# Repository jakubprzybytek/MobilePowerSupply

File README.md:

# MobilePowerSupply
Mobile Power Supply

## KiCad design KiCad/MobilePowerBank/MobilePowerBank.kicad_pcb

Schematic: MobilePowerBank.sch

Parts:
C1, C5, C11, C28, C45, C46, C71: 47u/35V; CP_Tantalum_Case-D_EIA-7343-31_Reflow
C2, C29, C30, C47, C48, C72: 10u/50V/X7R; C_2220
C3: 4n7; C_0805
C4, C33, C34, C51, C52, C73, C74: 22n; C_0805
C6, C7, C8, C13, C15, C16, C18, C20, C26, C39, C40, C41, C42, C57, C58, C59, C60, C63, C65, C67, C69, C77, C78: 100n; C_0805
C9, C10, C35, C36, C37, C38, C53, C54, C55, C56: 47u/1-45mESR; CP_Tantalum_Case-D_EIA-7343-31_Reflow
C12: 220n; C_0805
C14: 47u/16V; CP_Tantalum_Case-C_EIA-6032-28_Reflow
C17: 47u/6.3V; CP_Tantalum_Case-C_EIA-6032-28_Reflow
C19, C21, C64, C66, C68, C70: 10u/6.3V; CP_Tantalum_Case-B_EIA-3528-21_Reflow
C22, C23: 10u/16V; CP_Tantalum_Case-B_EIA-3528-21_Reflow
C24, C25, C27, C43, C44, C61, C62, C79: 1u; C_0805
C31, C32: 10n; C_0805
C49, C50: 4u7; C_0805
C75: 330n / 50V; C_0805
C76: 22u/16V; CP_Elec_4x5.8
C80, C82, C83, C84, C85, C86: 1u/50V; C_1206
C81: 100u/6V3; C_1812
D1: LED; D_0805
F1: 5A; Fuseholder5x20_horiz_open_inline_Type-I
J1: Power IN; TerminalBlock_Altech_AK300-2_P5.00mm
J2: Power OUT 2; TerminalBlock_Altech_AK300-2_P5.00mm
J3: Power OUT 1; TerminalBlock_Altech_AK300-2_P5.00mm
J4: OLED I2C; OLED_0.96inch_128x64_I2C
J5: PDI; Pin_Header_Straight_2x03_Pitch2.54mm
J6: OLED; FPC_30
J7: Power OUT 3; TerminalBlock_Altech_AK300-2_P5.00mm
J8: Power OUT 4; TerminalBlock_Altech_AK300-2_P5.00mm
J9: Power OUT 5; TerminalBlock_Altech_AK300-2_P5.00mm
J10: Power OUT 6; TerminalBlock_Altech_AK300-2_P5.00mm
J11: PowerLED; JST_XH_B02B-XH-A_02x2.50mm_Straight
L1: 10u; L_1206
MH1, MH2, MH3, MH4: MountingHole_Pad; MountingHole_3.5mm
R1, R6, R87: 68k; R_0805
R2, R9, R10, R21, R38, R39, R66, R67: 2k2; R_0805
R3, R14, R16, R17, R18, R19, R48, R49, R50, R51, R52, R53, R76, R77, R78, R79, R80, R81, R94, R95, R96: 0R033; R_2512
R4, R15, R20, R36, R37, R54, R55, R64, R65, R82, R83, R97: 20k; R_0805
R5, R12, R86: 100k; R_0805
R7, R27, R33, R35, R61, R63: 300k; R_0805
R8, R11, R23, R24, R47, R73, R75, R93: 10k; R_0805
R13, R28: 4k7; R_0805
R22, R29, R31, R44, R57, R59: 47k; R_0805
R25: 1M; R_1206
R26, R30, R56, R58: 220k; R_0805
R32, R34, R60, R62: 30k; R_0805
R40, R41, R42, R43, R68, R69, R70, R71: 15k4; R_0805
R45: 3k9; R_0805
R46, R72, R74, R92: 90k; R_0805
R84, R85, R98: 0; R_0805
R88: 11k; R_0805
R89: 1k5; R_0805
R90: 7k68; R_0805
R91: 200; R_0805
R99: 3k3; R_0805
SW1: SW_DIP_x01; Pin_Header_Angled_1x02_Pitch2.54mm
U1, U4, U9, U10, U13, U14, U16: INA139; SOT-23-5
U2, U7, U8: LMZ14203H; TO-263-7_TabPin4
U3: L78M12; TO-252-2_Rectifier
U5: UA78M33; TO-252-2_Rectifier
U6: LMZ14203; TO-263-7_TabPin4
U11, U12: LMZ14201H; TO-263-7_TabPin4
U15: ATXMEGA256A3U-AU; TQFP-64_14x14mm_Pitch0.8mm
U17: L78L05_SOT89; SOT-89-3
x1, x2, x3, x4, x6, x7, x8: jumper; Jumper_33x1.5
x5, x9: jumper; Jumper_45x1.5

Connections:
+3V3: C16.1, C17.1, C18.1, C19.1, C24.1, C63.1, C64.1, C65.1, C66.1, C67.1, C68.1, C69.1, C70.1, D1.2, J4.1, J5.2, J6.19, J6.20, J6.21, L1.1, R9.2, R10.2, R23.2, R24.1, U5.3 (OUT), U15.15 (VCC), U15.25 (VCC), U15.35 (VCC), U15.45 (VCC), U15.53 (VCC)
/+3.3VA: C20.1, C21.1, L1.2, U15.61 (AVCC)
/OLED_!DS: J6.17, U15.28 (RXD0/OC0C/PD2)
/OLED_!RES: J6.16, U15.31 (PD5/OC1B/XCK1/MOSI)
/OLED_D0: J6.12, U15.36 (PE0/OC0A/SDA/SDAIN)
/OLED_D1: J6.11, U15.37 (PE1/OC0B/XCK0/SCL/SCLIN)
/OLED_D2: J6.10, U15.38 (PE2/OC0C/RXD0/SDAOUT)
/OLED_D3: J6.9, U15.39 (PE3/OC0D/TXD0/SCLOUT)
/OLED_D4: J6.8, U15.40 (PE4/OC1A/~SS~)
/OLED_D5: J6.7, U15.41 (PE5/OC1B/XCK1/MOSI)
/OLED_D6: J6.6, U15.42 (PE6/RXD1/MISO/TOSC2)
/OLED_D7: J6.5, U15.43 (PE7/TXD1/SCK/TOSC1)
/OLED_D/!C: J6.15, U15.29 (TXD0/OC0D/PD3)
/OLED_E/!RD: J6.13, U15.30 (PD4/OC1A/~SS~)
/OLED_R/!W: J6.14, U15.32 (PD6/RXD1/D-/MISO)
GND: C5.2, C6.2, C12.2, C13.2, C14.2, C15.2, C16.2, C17.2, C18.2, C19.2, C20.2, C21.2, C22.2, C23.2, C24.2, C25.2, C26.2, C27.2, C39.2, C40.2, C43.2, C44.2, C57.2, C58.2, C61.2, C62.2, C63.2, C64.2, C65.2, C66.2, C67.2, C68.2, C69.2, C70.2, C77.2, C79.2, J4.2, J5.6, J6.1, J6.29, R25.1, R98.1, SW1.1, U3.2 (GND), U5.2 (GND), U15.14 (GND), U15.24 (GND), U15.34 (GND), U15.44 (GND), U15.52 (GND), U15.60 (GND)
GNDA: C1.2, C2.2, C3.2, C7.1, C8.1, C9.2, C10.2, C11.2, C28.2, C29.2, C30.2, C31.2, C32.2, C35.2, C36.2, C37.2, C38.2, C41.1, C42.1, C45.2, C46.2, C47.2, C48.2, C49.2, C50.2, C53.2, C54.2, C55.2, C56.2, C59.1, C60.1, C71.2, C72.2, C73.2, C75.2, C76.2, C78.1, C80.2, C81.2, C82.2, C83.1, C84.2, C85.2, C86.2, J1.1, J2.2, J3.2, J7.2, J8.2, J9.2, J10.2, J11.2, R2.2, R4.2, R13.2, R15.2, R20.2, R21.2, R36.2, R37.2, R38.2, R39.2, R45.2, R47.2, R54.2, R55.2, R64.2, R65.2, R66.2, R67.2, R73.2, R75.2, R82.2, R83.2, R88.2, R89.2, R93.2, R97.2, R98.2, U1.2, U2.4, U4.2, U6.4, U7.4, U8.4, U9.2, U10.2, U11.4, U12.4, U13.2, U14.2, U16.2, x6.1 (A), x6.2 (B), x7.1 (A), x7.2 (B), x8.1 (A), x8.2 (B), x9.1 (A), x9.2 (B)
IN_Current: C25.1, R4.1, U1.1, U15.11 (TDI/AC5/ADC5/PB5)
IN_Voltage: C15.1, R1.2, R2.1, U15.12 (TCK/AC1OUT/AC6/ADC6/PB6)
LED: R8.1, U15.48 (PF2/OC0C/RXD0)
unnamed: C3.1, U2.5
unnamed: C4.2, R21.1, R22.1, U2.6
unnamed: C5.1, C6.1, U3.1 (IN), x5.2 (B)
unnamed: C4.1, C8.2, C9.1, C10.1, C83.2, R14.2, R18.2, R19.2, R28.2, U2.7, U4.3, U4.5
unnamed: C23.1, J6.3
unnamed: C31.1, U7.5
unnamed: C32.1, U8.5
unnamed: C33.1, C35.1, C37.1, C41.2, C84.1, R42.2, R48.2, R49.2, R50.2, U7.7, U9.3, U9.5
unnamed: C33.2, R38.1, R40.1, U7.6
unnamed: C34.1, C36.1, C38.1, C42.2, C82.1, R43.2, R51.2, R52.2, R53.2, U8.7, U10.3, U10.5
unnamed: C34.2, R39.1, R41.1, U8.6
unnamed: C49.1, U11.5
unnamed: C50.1, U12.5
unnamed: C51.1, C53.1, C55.1, C59.2, C85.1, R70.2, R76.2, R77.2, R78.2, U11.7, U13.3, U13.5
unnamed: C51.2, R66.1, R68.1, U11.6
unnamed: C52.1, C54.1, C56.1, C60.2, C86.1, R71.2, R79.2, R80.2, R81.2, U12.7, U14.3, U14.5
unnamed: C52.2, R67.1, R69.1, U12.6
unnamed: C73.1, U6.5
unnamed: C74.1, C78.2, C80.1, C81.1, R91.2, R94.2, R95.2, R96.2, U6.7, U16.3, U16.5
unnamed: C74.2, R89.1, R90.1, U6.6
unnamed: C76.1, J11.1, R99.1, U17.2 (GND)
unnamed: D1.1, R8.2
unnamed: J6.4, R25.2
unnamed: R5.2, U2.2
unnamed: R6.2, R7.1
unnamed: R11.2, R23.1, SW1.2
unnamed: R7.2, R20.1, U2.3
unnamed: R22.2, R28.1
unnamed: R26.2, R32.1
unnamed: R5.1, R27.2
unnamed: R29.2, R33.1
unnamed: R30.2, R34.1
unnamed: R31.2, R35.1
unnamed: R32.2, U7.2
unnamed: R33.2, R36.1, U7.3
unnamed: R34.2, U8.2
unnamed: R35.2, R37.1, U8.3
unnamed: R40.2, R42.1
unnamed: R41.2, R43.1
unnamed: R56.2, R60.1
unnamed: R57.2, R61.1
unnamed: R58.2, R62.1
unnamed: R59.2, R63.1
unnamed: R60.2, U11.2
unnamed: R61.2, R64.1, U11.3
unnamed: R62.2, U12.2
unnamed: R63.2, R65.1, U12.3
unnamed: R68.2, R70.1
unnamed: R69.2, R71.1
unnamed: R84.2, R86.1
unnamed: R85.2, R87.1
unnamed: R86.2, U6.2
unnamed: R87.2, R88.1, U6.3
unnamed: R90.2, R91.1
unnamed: R99.2, U17.1 (OUT)
OUT_1_Current: C27.1, R15.1, U4.1, U15.3 (AC5/ADC5/PA5)
OUT_1_Voltage: C26.1, R12.2, R13.1, U15.4 (AC1OUT/AC6/ADC6/PA6)
OUT_2_Current: C43.1, R54.1, U9.1, U15.1 (AC3/ADC3/PA3)
OUT_2_Voltage: C39.1, R44.2, R45.1, U15.2 (AC4/ADC4/PA4)
OUT_3_Current: C44.1, R55.1, U10.1, U15.63 (AC1/ADC1/PA1)
OUT_3_Voltage: C40.1, R46.2, R47.1, U15.64 (AC2/ADC2/PA2)
OUT_4_Current: C61.1, R82.1, U13.1, U15.7 (AC1/ADC1/PB1)
OUT_4_Voltage: C57.1, R72.2, R73.1, U15.8 (DAC0/AC2/ADC2/PB2)
OUT_5_Current: C62.1, R83.1, U14.1, U15.5 (AC0OUT/AC7/ADC7/PA7)
OUT_5_Voltage: C58.1, R74.2, R75.1, U15.6 (AREFB/AC0/ADC0/PB0)
OUT_6_Current: C79.1, R97.1, U15.9 (DAC1/AC3/ADC3/PB3), U16.1
OUT_6_Voltage: C77.1, R92.2, R93.1, U15.10 (TMS/AC4/ADC4/PB4)
PDI_CLK: J5.5, R24.2, U15.57 (~RESET~/PDI_CLK)
PDI_DATA: J5.1, U15.56 (PDI_DATA)
POWER_1_OUT: J3.1, R12.1, R14.1, R18.1, R19.1, U4.4
POWER_2_OUT: J2.1, R44.1, R48.1, R49.1, R50.1, U9.4
POWER_3_OUT: J7.1, R46.1, R51.1, R52.1, R53.1, U10.4
POWER_4_OUT: J8.1, R72.1, R76.1, R77.1, R78.1, U13.4
POWER_5_OUT: J9.1, R74.1, R79.1, R80.1, R81.1, U14.4
POWER_6_OUT: J10.1, R92.1, R94.1, R95.1, R96.1, U16.4
POWER_IN: C11.1, C29.1, R3.1, R16.1, R17.1, R26.1, R29.1, U1.4, U7.1, x1.1 (A), x2.1 (A)
POWER_IN_1: C1.1, C2.1, R6.1, R27.1, U2.1, x2.2 (B), x3.1 (A)
POWER_IN_3: C28.1, C30.1, R30.1, R31.1, U8.1, x1.2 (B)
POWER_IN_4: C45.1, C46.1, C47.1, C48.1, R56.1, R57.1, R58.1, R59.1, U11.1, U12.1, x3.2 (B), x4.1 (A)
POWER_IN_6: C71.1, C72.1, R84.1, R85.1, U6.1, x4.2 (B), x5.1 (A)
SCK: J4.3, R9.1, U15.17 (SCLIN/SCL/XCK0/OC0AHS/OC0B/PC1)
SDA: J4.4, R10.1, U15.16 (SDAIN/SDA/~OC0ALS~/OC0A/PC0)
SWITCH: C12.1, R11.1, U15.49 (PF3/OC0D/TXD0)
Unfused_Power: C75.1, F1.1, J1.2, U17.3 (IN)
VDD: C7.2, F1.2, R1.1, R3.2, R16.2, R17.2, U1.3, U1.5

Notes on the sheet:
Dell Vout = 19.6V Iout(max) = 3A Uen = 22.9V SS 1 (Soft start order)
ASI1600 Vout = 12V Iout(max) = 3A SS 2
EQ6-R Vout = 12V Iout(max) = 3A SS 2
Moonlite Vout = 12V Iout(max) = 1A SS 1
FlatField Vout = 12V Iout(max) = 1A SS 1
USB Vout = 5V Iout(max) = 3A ss 3
R=5V/5mA=1k
3.9/(47+3.9) * 12V = 0.92V
4.7/(100+4.7) * 12V = 0.90V
2k2/(2k2+68k)=0.03 (1/32)

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
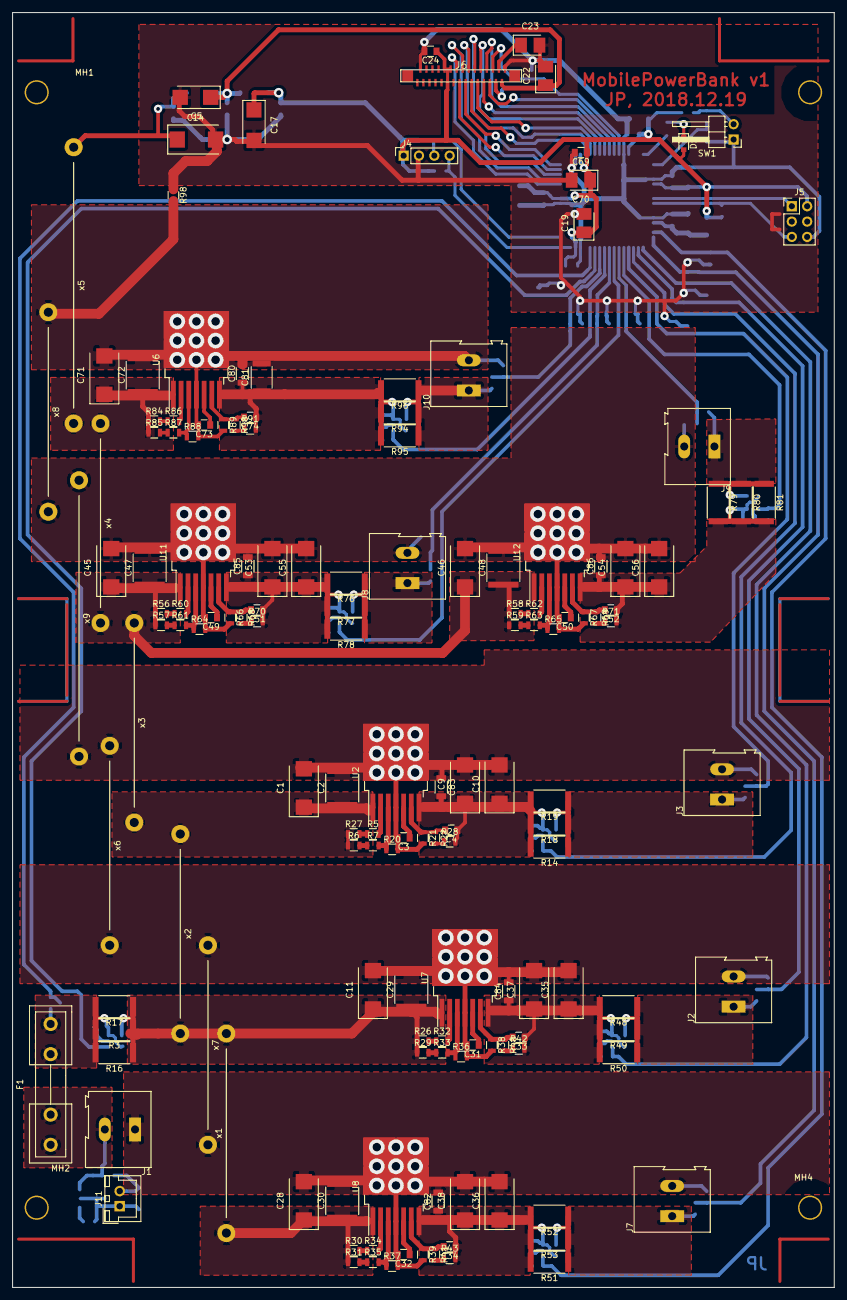
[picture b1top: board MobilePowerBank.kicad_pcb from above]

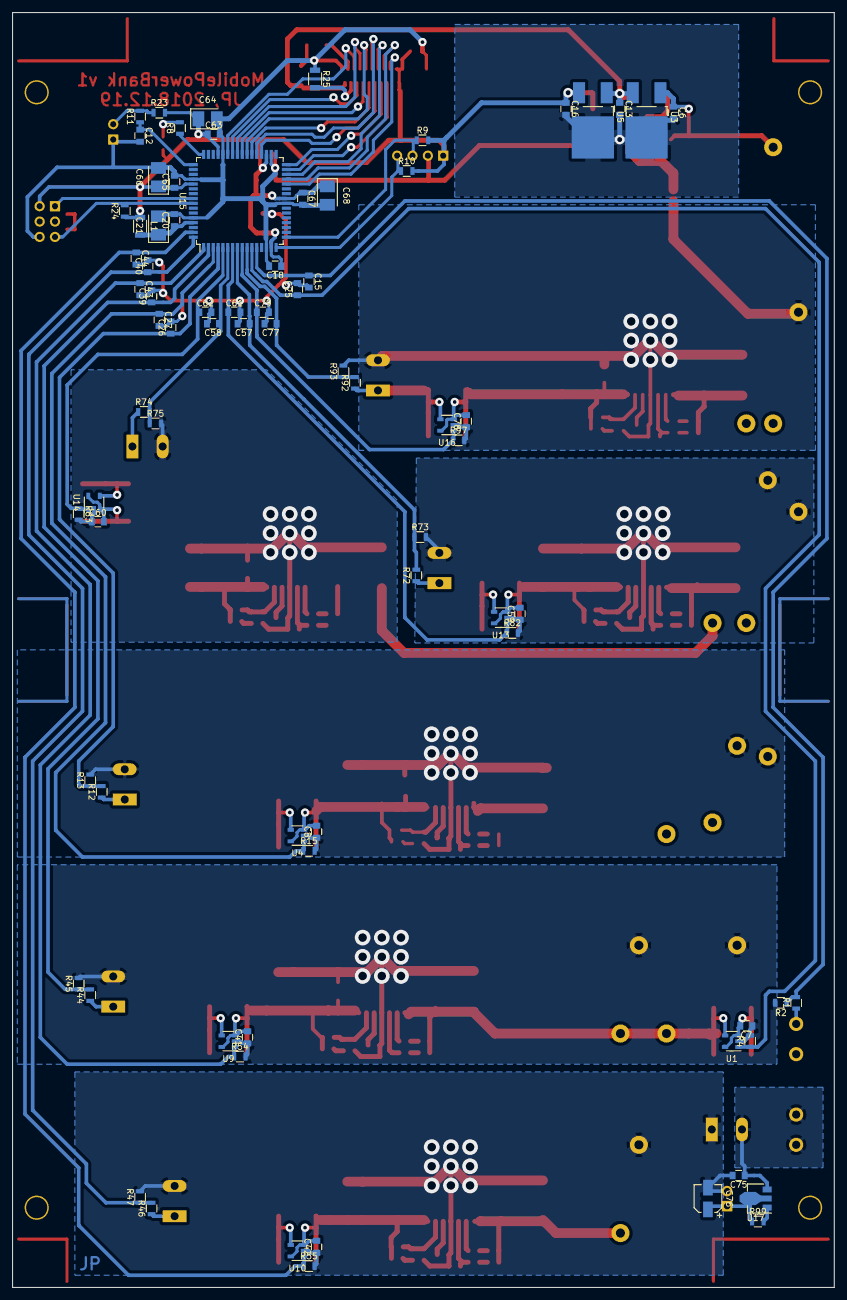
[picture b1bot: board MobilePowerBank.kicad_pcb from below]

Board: 2 copper layers, 136.0 x 211.0 mm, 230 parts (77 on the bottom side), 106 nets.

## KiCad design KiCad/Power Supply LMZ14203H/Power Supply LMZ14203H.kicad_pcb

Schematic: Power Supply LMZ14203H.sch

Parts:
C1, C5, C14: 100u; CP_Elec_6.3x7.7
C2: 10u/35V/X7R; C_2220
C3: 4u7; C_0805
C4: 22n; C_0805
C6, C7, C8, C13, C15, C16, C18, C20, C26: 100n; C_0805
C9, C10: 47u/1-45mESR; CP_Tantalum_Case-D_EIA-7343-31_Reflow
C12: 10n; C_0805
C17: 47u; CP_Elec_6.3x5.8
C19, C21, C22, C23: 10u; CP_Elec_4x5.8
C24, C25, C27: 1u; C_0805
D1: LED; D_0805
F1: 5A; Fuseholder5x20_horiz_open_inline_Type-I
J1: Power IN; TerminalBlock_Altech_AK300-2_P5.00mm
J3: Power OUT; TerminalBlock_Altech_AK300-2_P5.00mm
J4: OLED I2C; OLED_0.96inch_128x64_I2C
J5: PDI; Pin_Header_Straight_2x03_Pitch2.54mm
J6: OLED; FPC_30
L1: 10u; L_1206
R1: 68k; R_0805
R2, R9, R10, R21: 2k2; R_0805
R3, R14, R16, R17, R18, R19: 0R1; R_2512
R4, R15, R20: 20k; R_0805
R5, R6: 30k; R_0805
R7: 300k; R_0805
R8, R11, R13, R23, R24: 10k; R_0805
R12: 90k; R_0805
R22, R28: 15k4; R_0805
R25: 1M; R_1206
R26: 0; R_0805
R27: 220k; R_0805
SW1: SW_DIP_x01; SW_SPST_B3S-1000
U1, U4: INA169; SOT-23-5
U2: LMZ14203H; TO-263-7_TabPin4
U3: L78M12; TO-252-2_Rectifier
U5: UA78M33; TO-252-2_Rectifier
U6: ATXMEGA32E5-AU; TQFP-32_7x7mm_Pitch0.8mm

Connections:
+3V3: C16.1, C17.1, C18.1, C19.1, C24.1, D1.2, J4.1, J5.2, J6.19, J6.20, J6.21, L1.1, R9.2, R10.2, R23.2, R24.1, U5.3, U6.17 (VCC)
+12V: C13.1, C14.1, C22.1, J6.2, U3.3, U5.1
/+3.3VA: C20.1, C21.1, L1.2, U6.32 (AVCC)
/OLED_!DS: J6.17, U6.21 (PD7/ADC15/TXD0/IN3/CLKOUT/EVOUT/AC0OUT)
/OLED_!RES: J6.16, U6.22 (PD6/ADC14/RXD0/IN0/RTCOUT/AC1OUT)
/OLED_D0: J6.12, U6.9 (AC0OUT/IN3/MOSI/TXD0/OC4DHS/OC4D/PC7)
/OLED_D1: J6.11, U6.10 (AC1OUT/IN0/MISO/RXD0/~OC4DLS~/OC4C/PC6)
/OLED_D2: J6.10, U6.11 (IN2/SCK/XCK0/OC5B/OC4CHS/OC4B/PC5)
/OLED_D3: J6.9, U6.12 (EXTCLK/OUT0/IN1/~SS~/OC5A/~OC4CLS~/OC4A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)
/OLED_D4: J6.8, U6.13 (IN3/TXD0/OC4BHS/OC4D/PC3)
/OLED_D5: J6.7, U6.14 (IN0/RXD0/~OC4BLS~/OC4C/PC2)
/OLED_D6: J6.6, U6.15 (IN2/SCL/XCK0/OC4AHS/OC4B/PC1)
/OLED_D7: J6.5, U6.16 (OUT0/IN1/SDA/~OC4ALS~/OC4A/PC0)
/OLED_D/!C: J6.15, U6.23 (PD5/ADC13/OC5B/XCK0/IN2)
/OLED_E/!RD: J6.13, U6.25 (PD3/ADC11/TXD0/IN3/OC1)
/OLED_R/!W: J6.14, U6.24 (PD4/ADC12/OC5A/IN1/OUT0/CLKOUT/EVOUT)
GND: C5.2, C6.2, C7.1, C8.1, C12.2, C13.2, C14.2, C15.2, C16.2, C17.2, C18.2, C19.2, C20.2, C21.2, C22.2, C23.2, C24.2, C25.2, C26.2, C27.2, J4.2, J5.6, J6.1, J6.29, R2.2, R4.2, R13.2, R15.2, R25.1, R26.1, SW1.1, U1.2, U3.2, U4.2, U5.2, U6.1 (GND), U6.18 (GND)
GNDA: C1.2, C2.2, C3.2, C9.2, C10.2, J1.1, J3.2, R20.2, R21.2, R26.2, U2.4
IN_Current: C25.1, R4.1, U1.1, U6.3 (DAC1/AC3/ADC3/PA3)
IN_Voltage: C15.1, R1.2, R2.1, U6.4 (DAC0/AC2/ADC2/PA2)
LED: R8.1, U6.30 (AC1OUT/AC6/ADC6/PA6)
unnamed: C1.1, C2.1, R3.1, R6.1, R16.1, R17.1, R27.1, U1.4, U2.1
unnamed: C3.1, U2.5
unnamed: C4.2, R21.1, R22.1, U2.6
unnamed: C4.1, C8.2, C9.1, C10.1, R12.1, R14.2, R18.2, R19.2, R28.2, U2.7, U4.3, U4.5
unnamed: C23.1, J6.3
unnamed: D1.1, R8.2
unnamed: F1.1, J1.2
unnamed: J6.4, R25.2
unnamed: R5.2, U2.2
unnamed: R6.2, R7.1
unnamed: R11.2, R23.1, SW1.2
unnamed: R7.2, R20.1, U2.3
unnamed: R22.2, R28.1
unnamed: R5.1, R27.2
OUT_Current: C27.1, R15.1, U4.1, U6.6 (AREF/AC0/ADC0/PA0)
OUT_Voltage: C26.1, R12.2, R13.1, U6.5 (AC1/ADC1/PA1)
PDI_CLK: J5.5, R24.2, U6.8 (~RESET~/PDI_CLK)
PDI_DATA: J5.1, U6.7 (PDI_DATA)
POWER_IN: C5.1, C6.1, C7.2, F1.2, R1.1, R3.2, R16.2, R17.2, U1.3, U1.5, U3.1
POWER_OUT: J3.1, R14.1, R18.1, R19.1, U4.4
SCK: J4.3, R9.1, U6.27 (PD1/ADC1/XCK0/SCL/IN2)
SDA: J4.4, R10.1, U6.28 (PD0/ADC8/SDA/IN1/OUT0/AREF)
SWITCH: C12.1, R11.1, U6.29 (AC0OUT/AC7/ADC7/PA7)

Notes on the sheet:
Vout = 12V Iout(max) = 3A
Enable range 1.18-6.50V Rup/Rdown = (Uin/1.18)-1

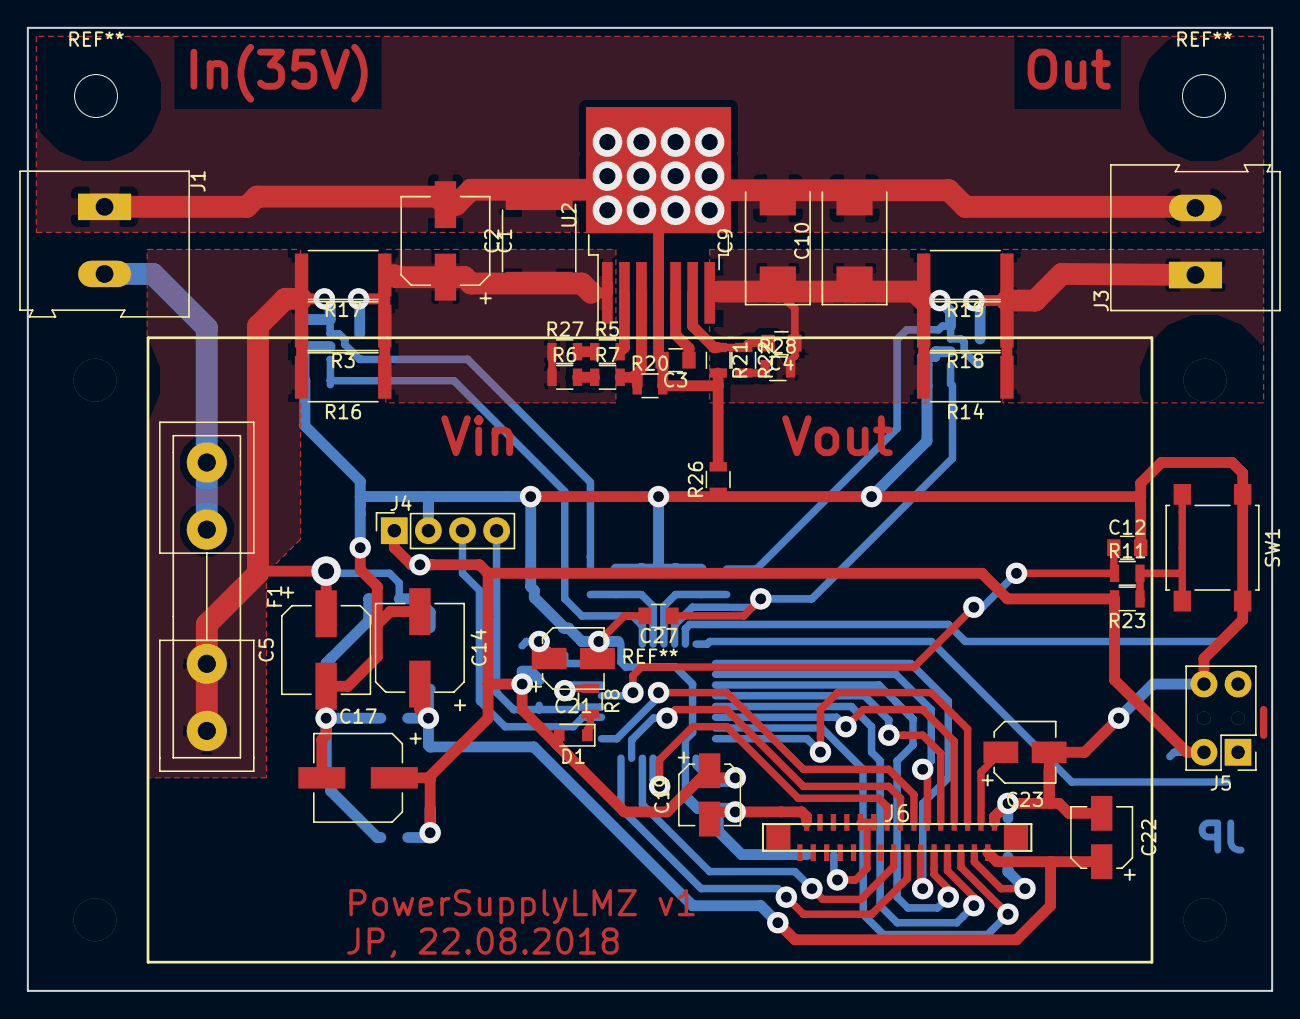
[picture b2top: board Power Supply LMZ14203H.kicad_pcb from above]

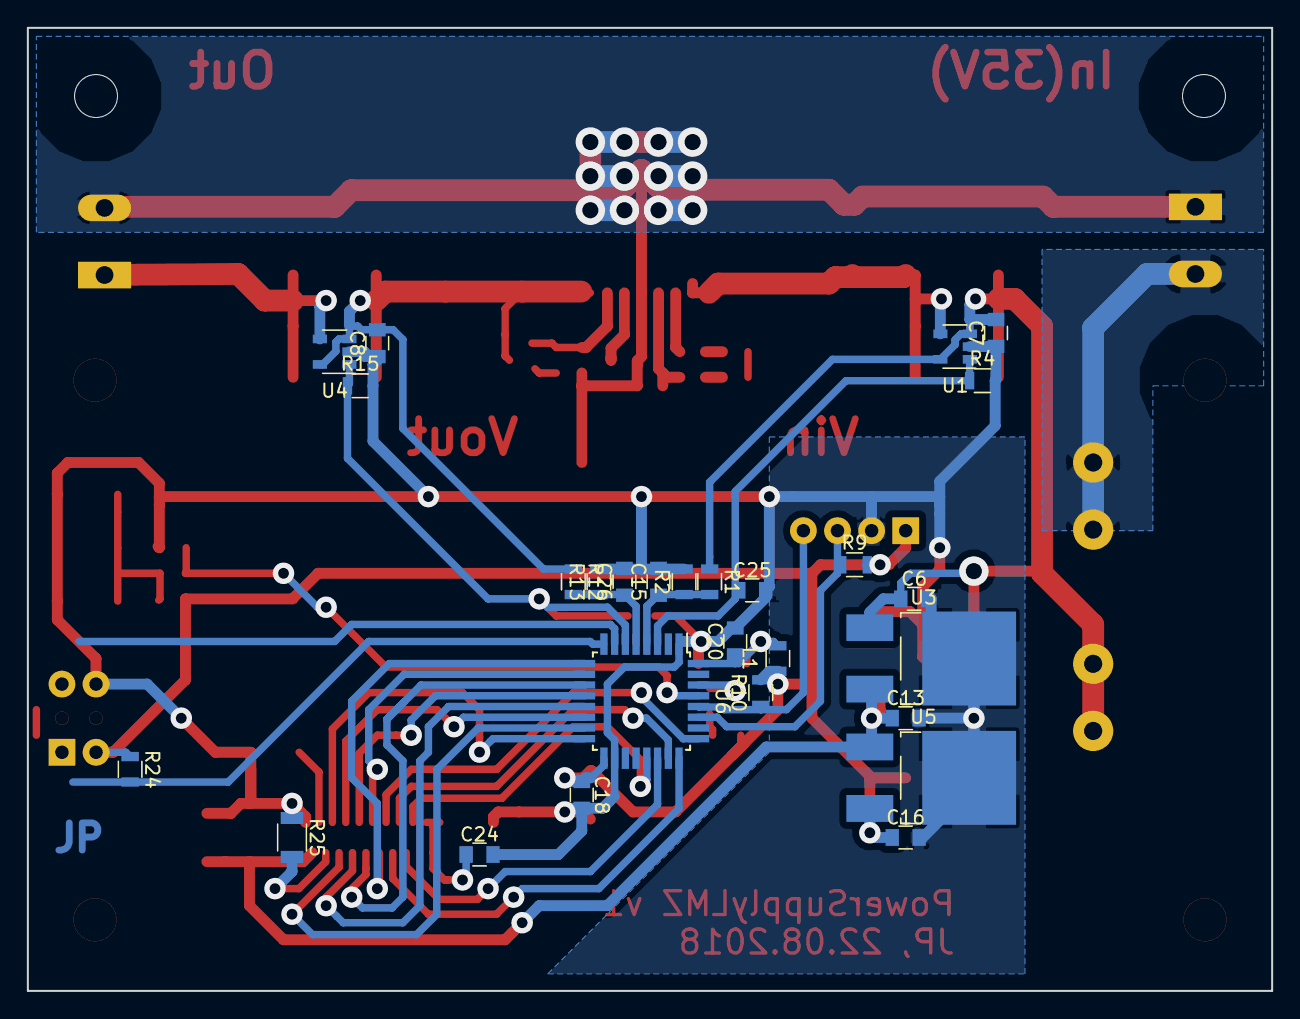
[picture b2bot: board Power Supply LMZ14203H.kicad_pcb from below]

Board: 2 copper layers, 92.7 x 71.8 mm, 69 parts (27 on the bottom side), 44 nets.

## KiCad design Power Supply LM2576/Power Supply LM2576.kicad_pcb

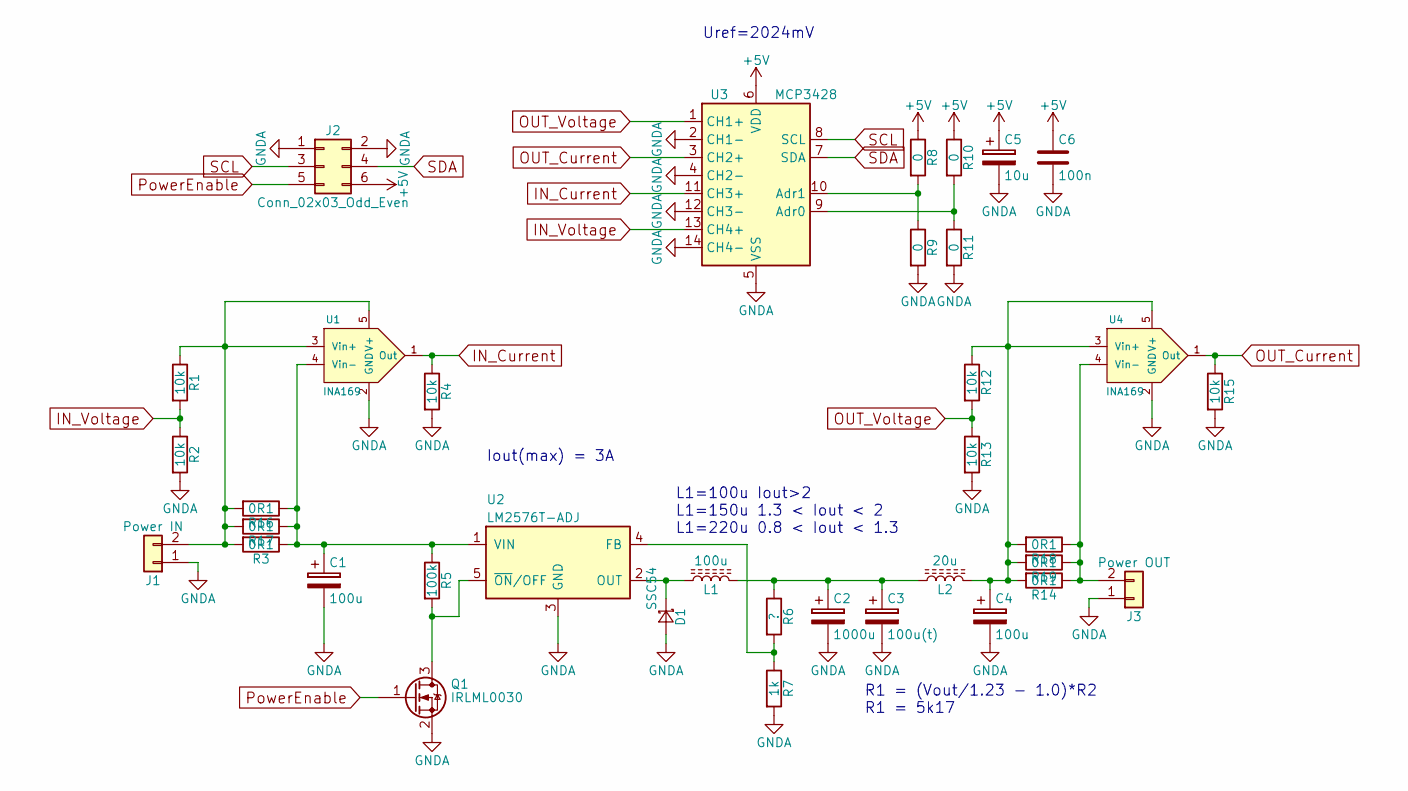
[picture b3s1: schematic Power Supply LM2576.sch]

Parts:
C1: 100u; CP_Radial_D8.0mm_P2.50mm
C2: 1000u; CP_Radial_D10.0mm_P2.50mm
C3: 100u(t); CP_Tantalum_Case-D_EIA-7343-31_Reflow
C4: 100u; CP_Radial_D6.3mm_P2.50mm
C5: 10u; CP_Radial_D6.3mm_P2.50mm
C6: 100n; C_0805
D1: SSC54; D_SMC
J1: Power IN; Pin_Header_Straight_1x02_Pitch2.54mm
J2: Conn_02x03_Odd_Even; Pin_Header_Straight_2x03_Pitch2.54mm
J3: Power OUT; Pin_Header_Straight_1x02_Pitch2.54mm
L1: 100u; L_Toroid_Vertical_L26.7mm_W14.0mm_P10.16mm_Pulse_D
L2: 20u; L_Toroid_Vertical_L16.8mm_W9.2mm_P7.10mm_Vishay_TJ3
Q1: IRLML0030; SOT-23
R1, R2, R4, R12, R13, R15: 10k; R_0805
R3, R14, R16, R17, R18, R19: 0R1; R_2512
R5: 100k; R_0805
R6: ?; R_0805
R7: 1k; R_0805
R8, R9, R10, R11: 0; R_0805
U1, U4: INA169; SOT-23-5
U2: LM2576T-ADJ; TO-220-5_Vertical_StaggeredType1
U3: MCP3428; SOIC-14_3.9x8.7mm_Pitch1.27mm

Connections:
+5V: C5.1, C6.1, J2.6, R8.1, R10.1, U3.6 (VDD)
GNDA: C1.2, C2.2, C3.2, C4.2, C5.2, C6.2, D1.2 (A), J1.1, J2.1, J2.2, J3.1, Q1.2 (S), R2.2, R4.2, R7.2, R9.2, R11.2, R13.2, R15.2, U1.2 (GND), U2.3 (GND), U3.2 (CH1-), U3.4 (CH2-), U3.5 (VSS), U3.12 (CH3-), U3.14 (CH4-), U4.2 (GND); also elsewhere on the board
IN_Current: R4.1, U1.1 (Out), U3.11 (CH3+)
IN_Voltage: R1.2, R2.1, U3.13 (CH4+)
unnamed: C1.1, R3.1, R5.1, R16.1, R17.1, U1.4 (Vin-), U2.1 (VIN)
unnamed: C2.1, C3.1, L1.2, L2.1, R6.1
unnamed 6: C4.1, L2.2, R12.1, R14.2, R18.2, R19.2, U4.3 (Vin+), U4.5 (V+); also elsewhere on the board
unnamed 7: J1.2, R1.1, R3.2, R16.2, R17.2, U1.3 (Vin+), U1.5 (V+); also elsewhere on the board
unnamed: D1.1 (K), L1.1, U2.2 (OUT)
unnamed: J3.2, R14.1, R18.1, R19.1, U4.4 (Vin-)
unnamed: Q1.3 (D), R5.2, U2.5 (~ON~/OFF)
unnamed: R6.2, R7.1, U2.4 (FB)
unnamed: R8.2, R9.1, U3.10 (Adr1)
unnamed: R10.2, R11.1, U3.9 (Adr0)
OUT_Current: R15.1, U3.3 (CH2+), U4.1 (Out)
OUT_Voltage: R12.2, R13.1, U3.1 (CH1+)
PowerEnable: J2.5, Q1.1 (G)
SCL: J2.3, U3.8 (SCL)
SDA: J2.4, U3.7 (SDA)

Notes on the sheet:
R1 = (Vout/1.23 - 1.0)*R2 R1 = 5k17
L1=100u Iout>2 L1=150u 1.3 < Iout < 2 L1=220u 0.8 < Iout < 1.3
Iout(max) = 3A
Uref=2024mV

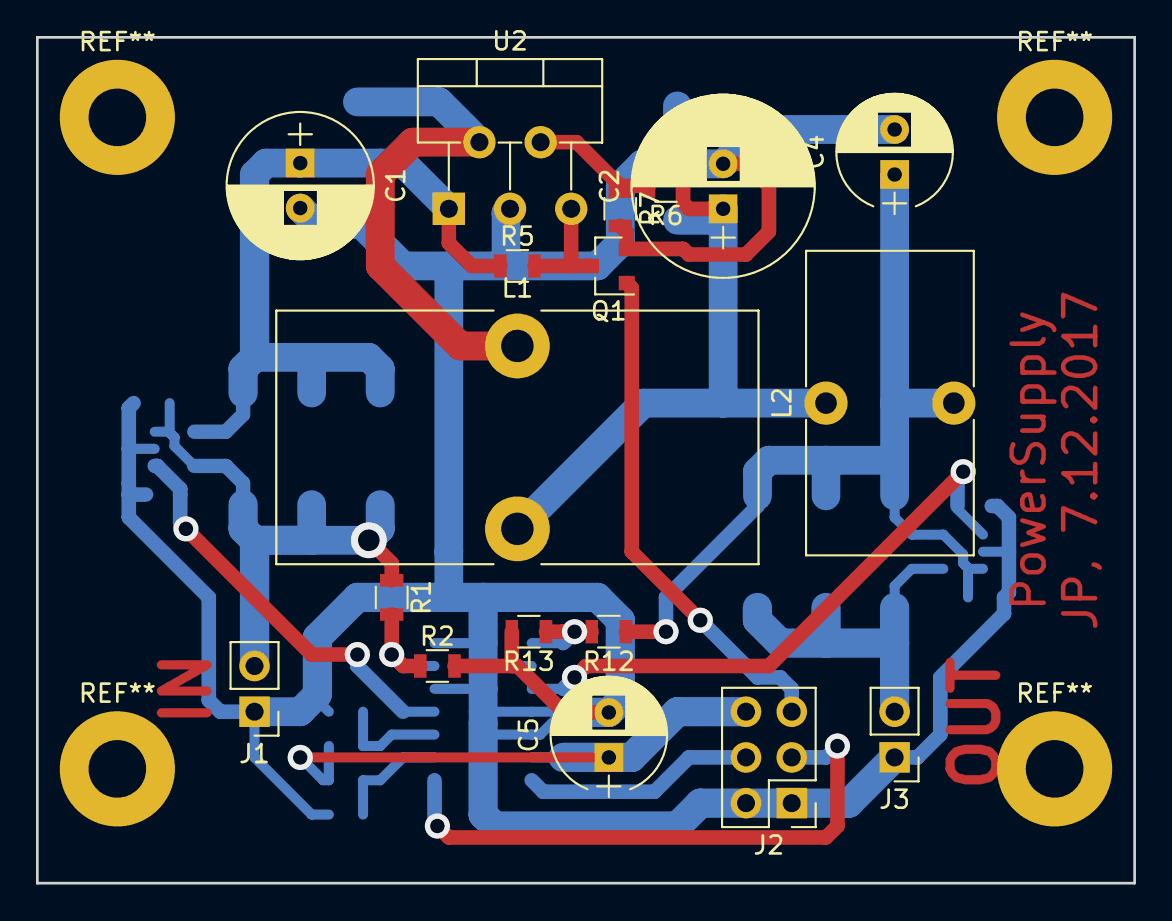
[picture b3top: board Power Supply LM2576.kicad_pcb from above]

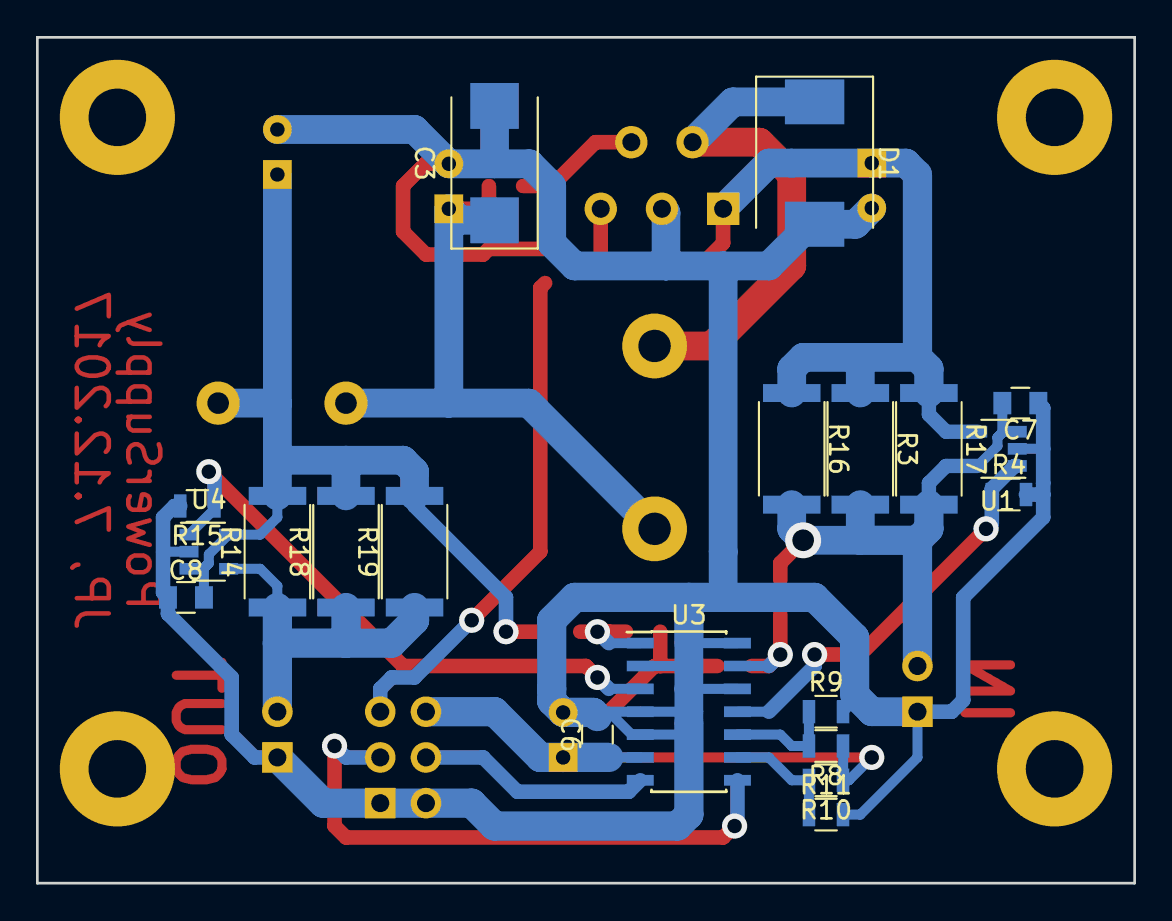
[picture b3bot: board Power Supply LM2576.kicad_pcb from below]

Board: 2 copper layers, 61.0 x 47.0 mm, 38 parts (20 on the bottom side), 19 nets.

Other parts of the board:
C7, C8: 100n; C_0805

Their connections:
GNDA: C7.1, C8.1; also elsewhere on the board
unnamed 6: C8.2; also elsewhere on the board
unnamed 7: C7.2; also elsewhere on the board

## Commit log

2017-11-08 Folder added
2017-11-09 ADC added for monitoring
2017-11-18 PCB init
2017-12-01 Some work on PCB
2017-12-05 PCB work
2017-12-07 Finishing PCB
2018-07-29 Changing folder structure
2018-08-11 LMZ14203H added
2018-08-14 CPU added
2018-08-15 Wirering
2018-08-15 Wirering done
2018-08-20 PCB proofing
2018-08-23 Some fixes
2018-09-23 Software init commit
2018-09-23 PCb fixes
2018-10-04 Screen.cpp added, some clean up, too
2018-10-04 More clean up
2018-10-04 RTC added
2018-10-07 MobilePowerBank init
2018-10-09 5 power supplies created
2018-10-11 xmega added
2018-10-11 Bigger case
2018-10-13 PCB major work
2018-10-15 PCB finish, BOM check
2018-10-24 Cap changed
2018-12-13 Aligning PCB
2018-12-14 Pimping PCB
2019-01-08 MobilePowerBank ADC first code
2019-01-09 DMA added
2019-01-10 DMA and screen
2019-01-27 Support for Output 3 added
2019-01-28 Added support for the switch
2019-01-30 Out 4 added
2019-02-20 Five outputs callibration
2019-02-24 Screen fixes
2019-02-24 Temperature readout routine added
2019-02-24 Mounting holes fixed to 4mm
2019-03-02 Storing data in EEPROM on power loss
2019-03-03 Reset button action implemented
2019-03-03 Added counter of writes to EEPROM
2019-04-13 Serial port added
2019-04-13 DMA stuff refactored. Not tested.
2019-04-13 Using DMA for USAR transmition
2019-04-13 UART communication
2019-04-13 Small refactor
2019-04-13 Improvement around events
2019-04-15 Fixing synchronisation issues
2019-05-01 Setting names for input and outputs using serial port
